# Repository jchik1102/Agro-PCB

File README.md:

# Agrobot Power Board

Native KiCad schematic and four-layer PCB draft for a regulated 12 V input with separate 5 V and 3.3 V buck converters. Designed as a documented portfolio project; **not a fabrication release or tested hardware**.

## Open it

1. Install KiCad 9 or newer, including its standard applications.
2. Extract this entire ZIP. Keep the project and Libraries folder together.
3. Open `Agrobot_Power_Board.kicad_pro` in KiCad.
4. Open the schematic with the Schematic Editor button, or the board with the PCB Editor button.
5. In PCB Editor, press **B** to fill the ground zones, then save. If any load/parse error appears, stop and send a screenshot of the complete error.
6. Press **Alt+3** for KiCad's 3D viewer. Included 3D bodies are simplified representations, not manufacturer CAD models.

Ground zones have been defined but are delivered unfilled. Until step 5, ground connections will appear incomplete. The supplied images and PDF are authoring previews, not screenshots or exports from KiCad.

## Requirements and status

| Item | Target / implementation | Evidence status |
| --- | --- | --- |
| Input | Regulated 12 V DC, screw terminal | Nominal design input; not qualified for battery/automotive transients |
| 5 V output | 0.75 A continuous, 1.5 A peak | Design target; load and thermal testing pending |
| 3.3 V output | 0.5 A continuous, 1.0 A peak | Design target; load and thermal testing pending |
| Ripple | 20 mVpp / 10 mVpp respectively, 20 MHz bandwidth | Targets only; not simulated or measured |
| Protection | Resettable input fuse, reverse-polarity diode, TVS clamp | Component-level proposal; coordination review pending |
| Board | 96 x 78 mm, four copper layers, four 3.2 mm mounting holes | Native layout draft |
| Ground | Two internal planes plus outer-layer zones | Fill locally before native DRC |

The two LMR33630 converters use separate inductors, feedback networks, and output capacitors. No microcontroller or sensors are included: this is the Agrobot **power-conditioning board** only. Peak duration is unspecified; no guaranteed peak-duration capability is claimed.

## Contents

- `.kicad_pro`, `.kicad_sch`, `.kicad_pcb`: editable native project.
- `Libraries`: project-local symbols, footprints, simplified 3D models.
- `Documentation/Schematic_Preview.pdf`: immediately viewable schematic preview.
- `Images`: illustrative top-board preview.

## Publishing on GitHub

Upload this folder's contents after reviewing the design. Keep the libraries and relative folder structure intact. The included `.gitignore` excludes local report runs and editor backups. You can deliberately add selected native PDFs, renders, and reviewed reports later.

An accurate project description is: "Developed a KiCad power-conditioning PCB draft for a 12 V input and 5 V/3.3 V outputs, with input protection and documented load/ripple targets. Fabrication and bench validation pending."

Do not describe the ripple or current targets as measured results, or this project as completed in Altium. AI-assisted authoring should be described accurately when relevant to portfolio or academic requirements.

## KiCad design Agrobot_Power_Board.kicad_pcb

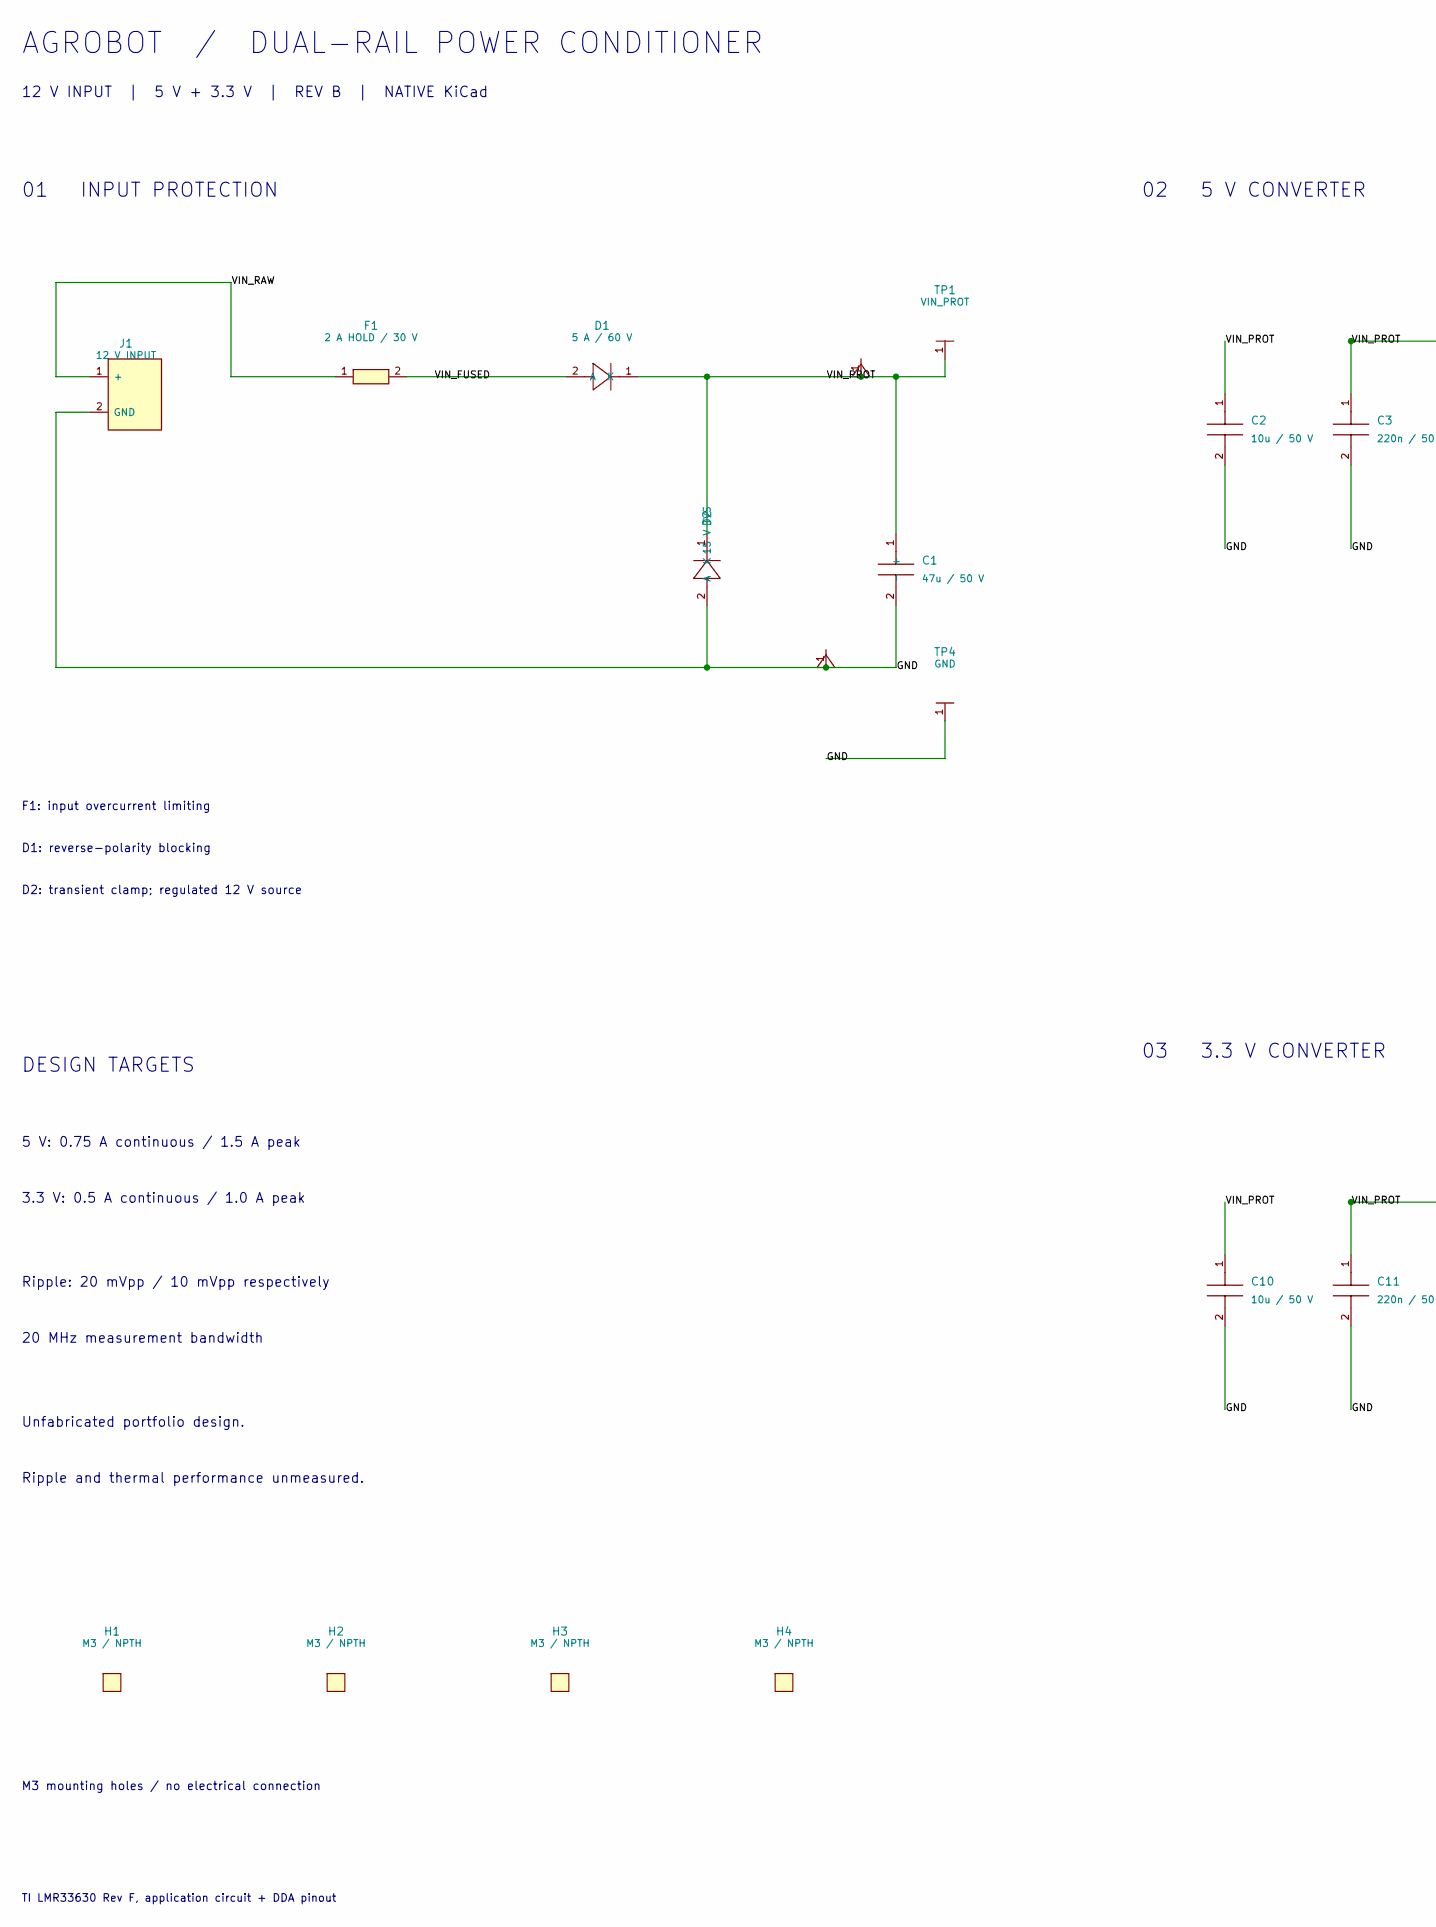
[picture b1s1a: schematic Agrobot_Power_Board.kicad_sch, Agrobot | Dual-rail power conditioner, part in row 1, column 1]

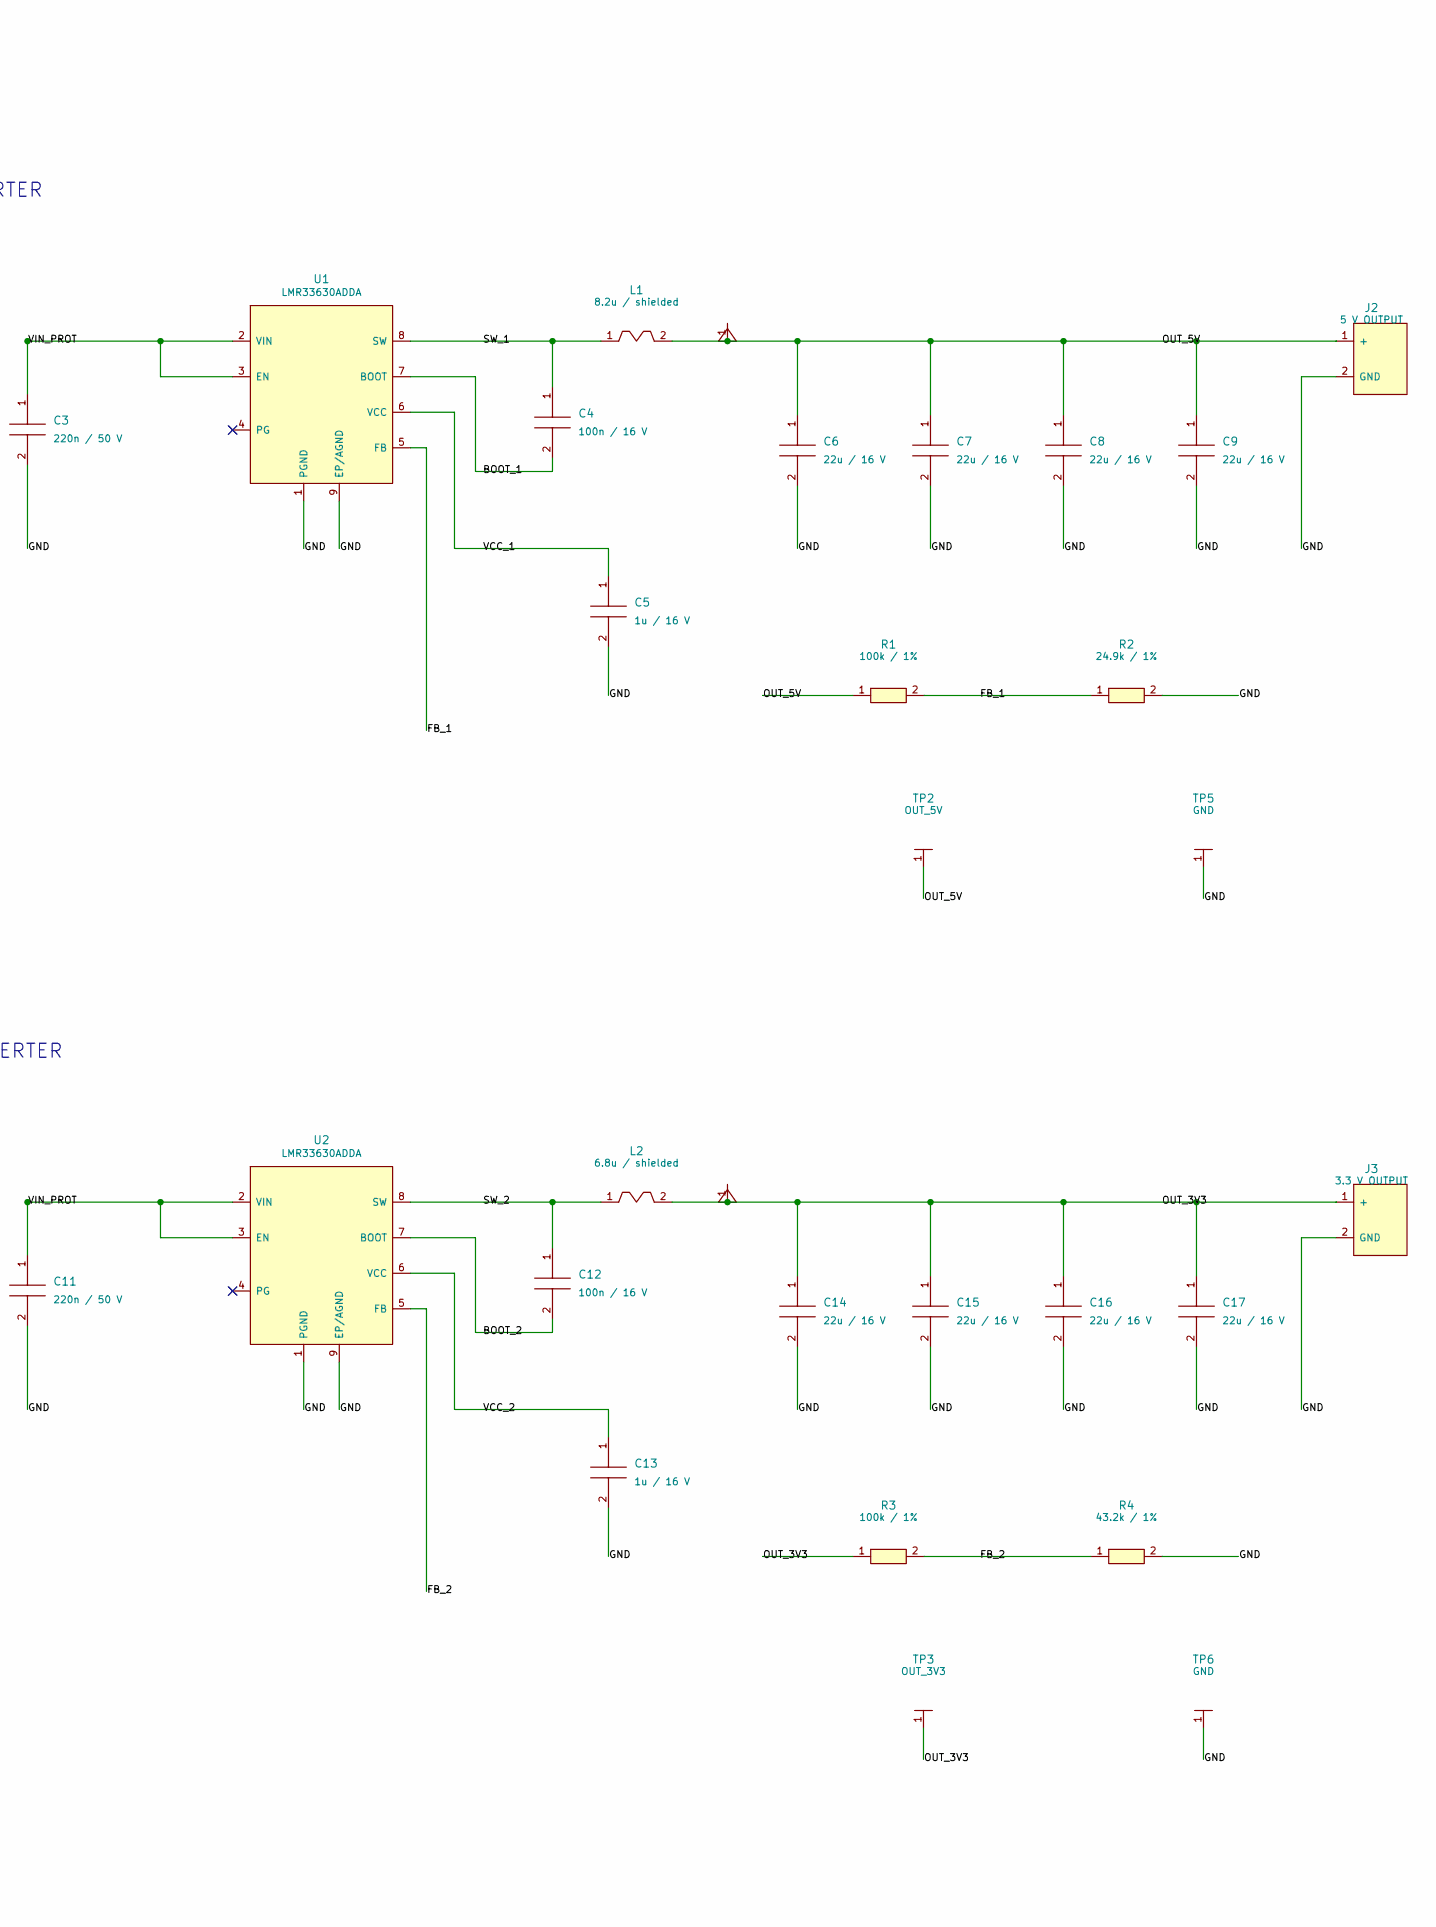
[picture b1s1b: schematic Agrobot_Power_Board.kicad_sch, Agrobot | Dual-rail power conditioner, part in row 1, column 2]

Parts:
C1: 47u / 50 V; Electro; MPN EEU-FR1H470
C2, C10: 10u / 50 V; C1210; MPN GRM32ER71H106KA12L
C3, C11: 220n / 50 V; C0805; MPN 0805 X7R 220nF 50V
C4, C12: 100n / 16 V; C0603; MPN 0603 X7R 100nF 16V
C5, C13: 1u / 16 V; C0805; MPN 0805 X7R 1uF 16V
C6, C7, C8, C9, C14, C15, C16, C17: 22u / 16 V; C1210; MPN 1210 X7R 22uF 16V
D1: 5 A / 60 V; SMC; MPN SS56-E3/57T
D2: 15 V TVS; SMB; MPN SMBJ15A
F1: 2 A HOLD / 30 V; PTC; MPN MF-R200
H1, H2, H3, H4: M3 / NPTH; Hole; MPN 3.2 mm non-plated hole
J1: 12 V INPUT; Terminal; MPN KF301-5.08-2P
J2: 5 V OUTPUT; Terminal; MPN KF301-5.08-2P
J3: 3.3 V OUTPUT; Terminal; MPN KF301-5.08-2P
L1: 8.2u / shielded; Inductor; MPN SRP1038A-8R2M
L2: 6.8u / shielded; Inductor; MPN SRP1038A-6R8M
R1, R3: 100k / 1%; R0805; MPN 0805 100k 1%
R2: 24.9k / 1%; R0805; MPN 0805 24.9k 1%
R4: 43.2k / 1%; R0805; MPN 0805 43.2k 1%
TP1: VIN_PROT; TP; MPN PCB test pad 2 mm
TP2: OUT_5V; TP; MPN PCB test pad 2 mm
TP3: OUT_3V3; TP; MPN PCB test pad 2 mm
TP4, TP5, TP6: GND; TP; MPN PCB test pad 2 mm
U1, U2: LMR33630ADDA; DDA; MPN LMR33630ADDAR

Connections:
BOOT_1: C4.2, U1.7
BOOT_2: C12.2, U2.7
FB_1: R1.2, R2.1, U1.5
FB_2: R3.2, R4.1, U2.5
GND: C1.2, C2.2, C3.2, C5.2, C6.2, C7.2, C8.2, C9.2, C10.2, C11.2, C13.2, C14.2, C15.2, C16.2, C17.2, D2.2, J1.2, J2.2, J3.2, R2.2, R4.2, TP4.1, TP5.1, TP6.1, U1.1, U1.9, U2.1, U2.9
OUT_3V3: C14.1, C15.1, C16.1, C17.1, J3.1, L2.2, R3.1, TP3.1
OUT_5V: C6.1, C7.1, C8.1, C9.1, J2.1, L1.2, R1.1, TP2.1
PG_1: U1.4
PG_2: U2.4
SW_1: C4.1, L1.1, U1.8
SW_2: C12.1, L2.1, U2.8
VCC_1: C5.1, U1.6
VCC_2: C13.1, U2.6
VIN_FUSED: D1.2, F1.2
VIN_PROT: C1.1, C2.1, C3.1, C10.1, C11.1, D1.1, D2.1, TP1.1, U1.2, U1.3, U2.2, U2.3
VIN_RAW: F1.1, J1.1

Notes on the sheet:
AGROBOT / DUAL-RAIL POWER CONDITIONER
12 V INPUT | 5 V + 3.3 V | REV B | NATIVE KiCad
01 INPUT PROTECTION
F1: input overcurrent limiting
D1: reverse-polarity blocking
D2: transient clamp; regulated 12 V source
02 5 V CONVERTER
03 3.3 V CONVERTER
DESIGN TARGETS
5 V: 0.75 A continuous / 1.5 A peak
3.3 V: 0.5 A continuous / 1.0 A peak
Ripple: 20 mVpp / 10 mVpp respectively
20 MHz measurement bandwidth
Unfabricated portfolio design.
Ripple and thermal performance unmeasured.
M3 mounting holes / no electrical connection
TI LMR33630 Rev F, application circuit + DDA pinout

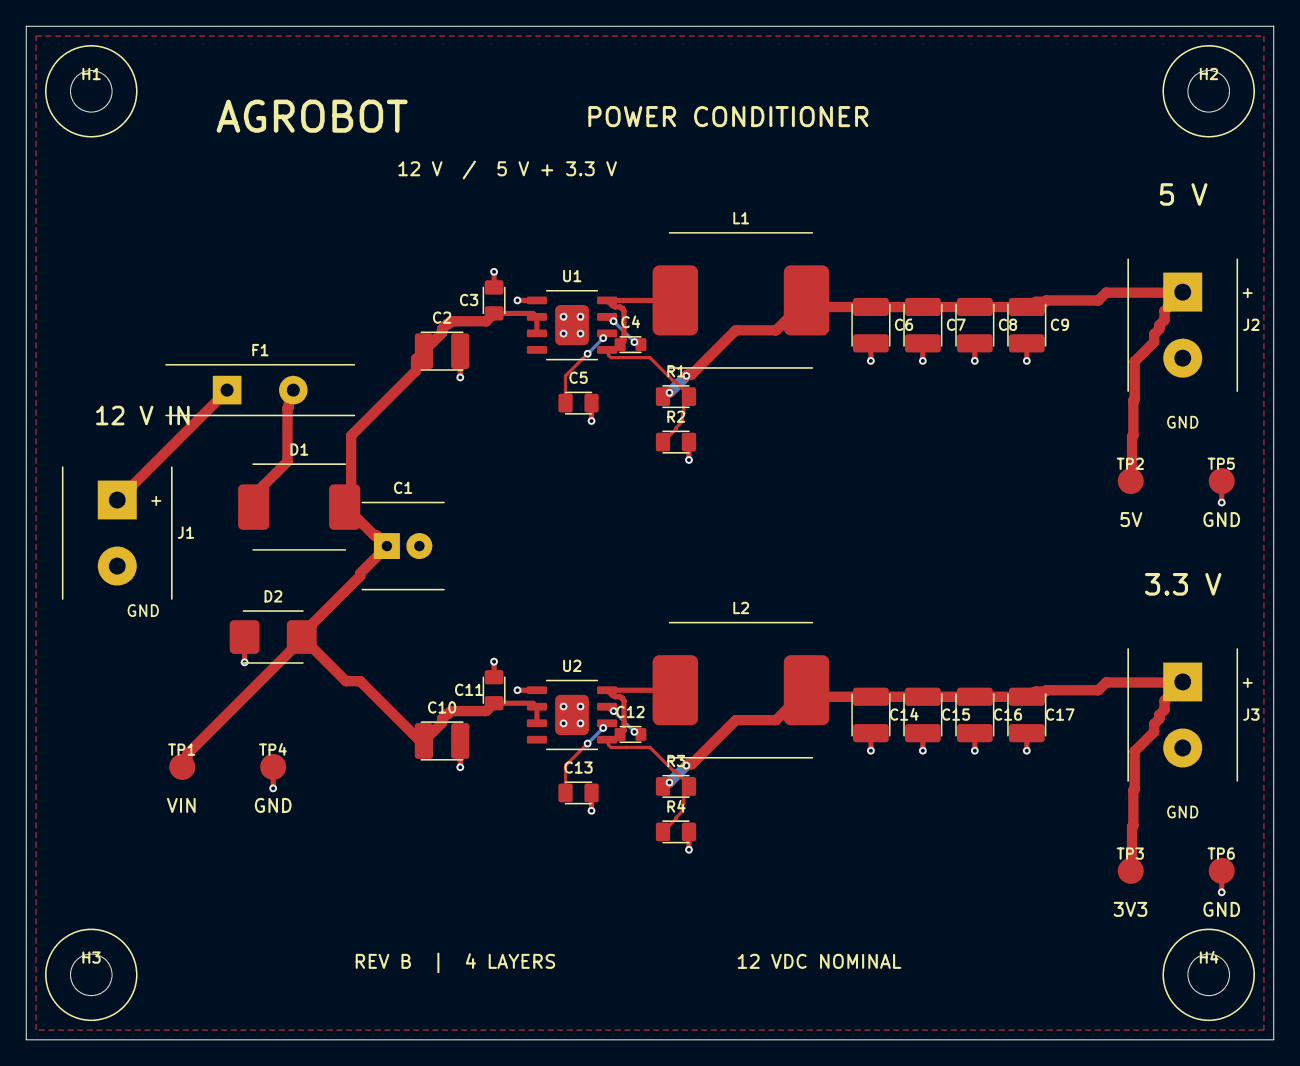
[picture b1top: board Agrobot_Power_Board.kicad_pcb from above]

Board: 4 copper layers, 96.0 x 78.0 mm, 41 parts (0 on the bottom side), 14 nets.

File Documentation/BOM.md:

# Bill of materials

Electrical selection list for the unbuilt Rev B design. Generic passive descriptions are procurement specifications, not fixed orderable part numbers. Exact passive variants and package tolerances require confirmation before purchasing.

| References | Qty | Value / rating | Part or selection | Local footprint |
|---|---:|---|---|---|
| J1 | 1 | 12 V INPUT | KF301-5.08-2P | Terminal |
| F1 | 1 | 2 A HOLD / 30 V | MF-R200 | PTC |
| D1 | 1 | 5 A / 60 V | SS56-E3/57T | SMC |
| D2 | 1 | 15 V TVS | SMBJ15A | SMB |
| C1 | 1 | 47u / 50 V | EEU-FR1H470 | Electro |
| U1, U2 | 2 | LMR33630ADDA | LMR33630ADDAR | DDA |
| L1 | 1 | 8.2u / shielded | SRP1038A-8R2M | Inductor |
| C2, C10 | 2 | 10u / 50 V | GRM32ER71H106KA12L | C1210 |
| C3, C11 | 2 | 220n / 50 V | 0805 X7R 220nF 50V | C0805 |
| C4, C12 | 2 | 100n / 16 V | 0603 X7R 100nF 16V | C0603 |
| C5, C13 | 2 | 1u / 16 V | 0805 X7R 1uF 16V | C0805 |
| C6, C7, C8, C9, C14, C15, C16, C17 | 8 | 22u / 16 V | 1210 X7R 22uF 16V | C1210 |
| R1, R3 | 2 | 100k / 1% | 0805 100k 1% | R0805 |
| R2 | 1 | 24.9k / 1% | 0805 24.9k 1% | R0805 |
| J2 | 1 | 5 V OUTPUT | KF301-5.08-2P | Terminal |
| L2 | 1 | 6.8u / shielded | SRP1038A-6R8M | Inductor |
| R4 | 1 | 43.2k / 1% | 0805 43.2k 1% | R0805 |
| J3 | 1 | 3.3 V OUTPUT | KF301-5.08-2P | Terminal |
| TP1 | 1 | VIN_PROT | PCB test pad 2 mm | TP |
| TP4, TP5, TP6 | 3 | GND | PCB test pad 2 mm | TP |
| TP2 | 1 | OUT_5V | PCB test pad 2 mm | TP |
| TP3 | 1 | OUT_3V3 | PCB test pad 2 mm | TP |
| H1, H2, H3, H4 | 4 | M3 / NPTH | 3.2 mm non-plated hole | Hole |

## Notes

- Resistors: 1%, 0805 imperial, at least 0.125 W.
- Ceramic capacitors: X7R, 10% nominal tolerance. Effective capacitance under DC bias has not been characterized.
- U1/U2: TI DDA HSOIC-8 with grounded exposed pad, 400 kHz variant.
- L1/L2: Bourns SRP1038A; 8.2 uH and 6.8 uH. Land geometry follows the 13.6 mm overall / 3.5 x 5.4 mm pad recommendation.
- F1: Bourns MF-R200 resettable PTC, 2 A hold, 30 V class. Time-current coordination is not qualified.
- D1: SS56 family SMC Schottky, 5 A / 60 V. Cathode faces VIN_PROT.
- D2: SMBJ15A unidirectional TVS; cathode to VIN_PROT. Not qualified for vehicle transients.
- Screw terminals: generic KF301 5.08 mm pitch. Match purchased part outline and wire-entry direction before assembly.
- H1-H4 are board holes, not purchased electronic parts. Test points are exposed PCB pads.
- All supplied 3D bodies are simplified illustrations rather than manufacturer STEP models.
